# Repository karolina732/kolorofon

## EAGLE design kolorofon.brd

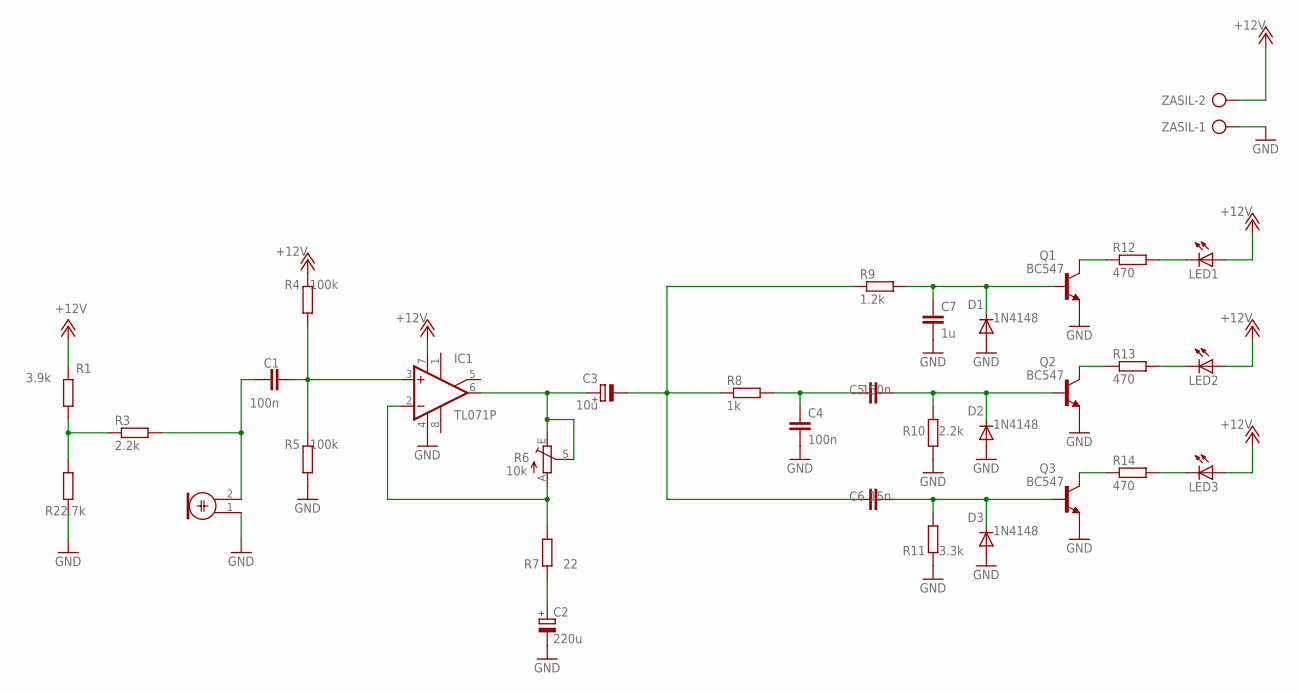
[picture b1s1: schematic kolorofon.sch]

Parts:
C1, C4: 100n; C050-025X075
C2: 220u; E2,5-6E
C3: 10u; E2-5
C5: 150n; C050-025X075
C6: 15n; C050-025X075
C7: 1u; C050-045X075
D1, D2, D3: 1N4148; DO35-7
IC1: TL071P; DIL08
LED1, LED2, LED3: LED5MM
M1: WM.64PN; WM-64PN
Q1, Q2, Q3: BC547; TO92
R1: 3.9k; 0204/7
R2: 2.7k; 0204/7
R3, R10: 2.2k; 0204/7
R4, R5: 100k; 0204/7
R6: 10k; S64Y
R7: 22; 0204/7
R8: 1k; 0204/7
R9: 1.2k; 0204/7
R11: 3.3k; 0204/7
R12, R13, R14: 470; 0204/7
ZASIL: AK300/2

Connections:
+12V: IC1.7 (V+), LED1.A, LED2.A, LED3.A, R1.1, R4.2, ZASIL.2
GND: C2.-, C4.2, C7.2, D1.A, D2.A, D3.A, IC1.4 (V-), M1.1, Q1.1 (E), Q2.1 (E), Q3.1 (E), R2.1, R5.1, R10.1, R11.1, ZASIL.1
unnamed: LED1.K (C), R12.2
unnamed: LED2.K (C), R13.2
unnamed: LED3.K (C), R14.2
unnamed: Q1.3 (C), R12.1
unnamed: Q2.3 (C), R13.1
unnamed: Q3.3 (C), R14.1
unnamed: C7.1, D1.C, Q1.2 (B), R9.2
unnamed: C5.2, D2.C, Q2.2 (B), R10.2
unnamed: C4.1, C5.1, R8.2
unnamed: C6.2, D3.C, Q3.2 (B), R11.2
unnamed: C3.-, C6.1, R8.1, R9.1
unnamed: C3.+, IC1.6 (OUT), R6.E, R6.S
unnamed: IC1.2 (-IN), R6.A, R7.2
unnamed: C2.+, R7.1
unnamed: C1.2, IC1.3 (+IN), R4.1, R5.2
unnamed: C1.1, M1.2, R3.2
unnamed: R1.2, R2.2, R3.1

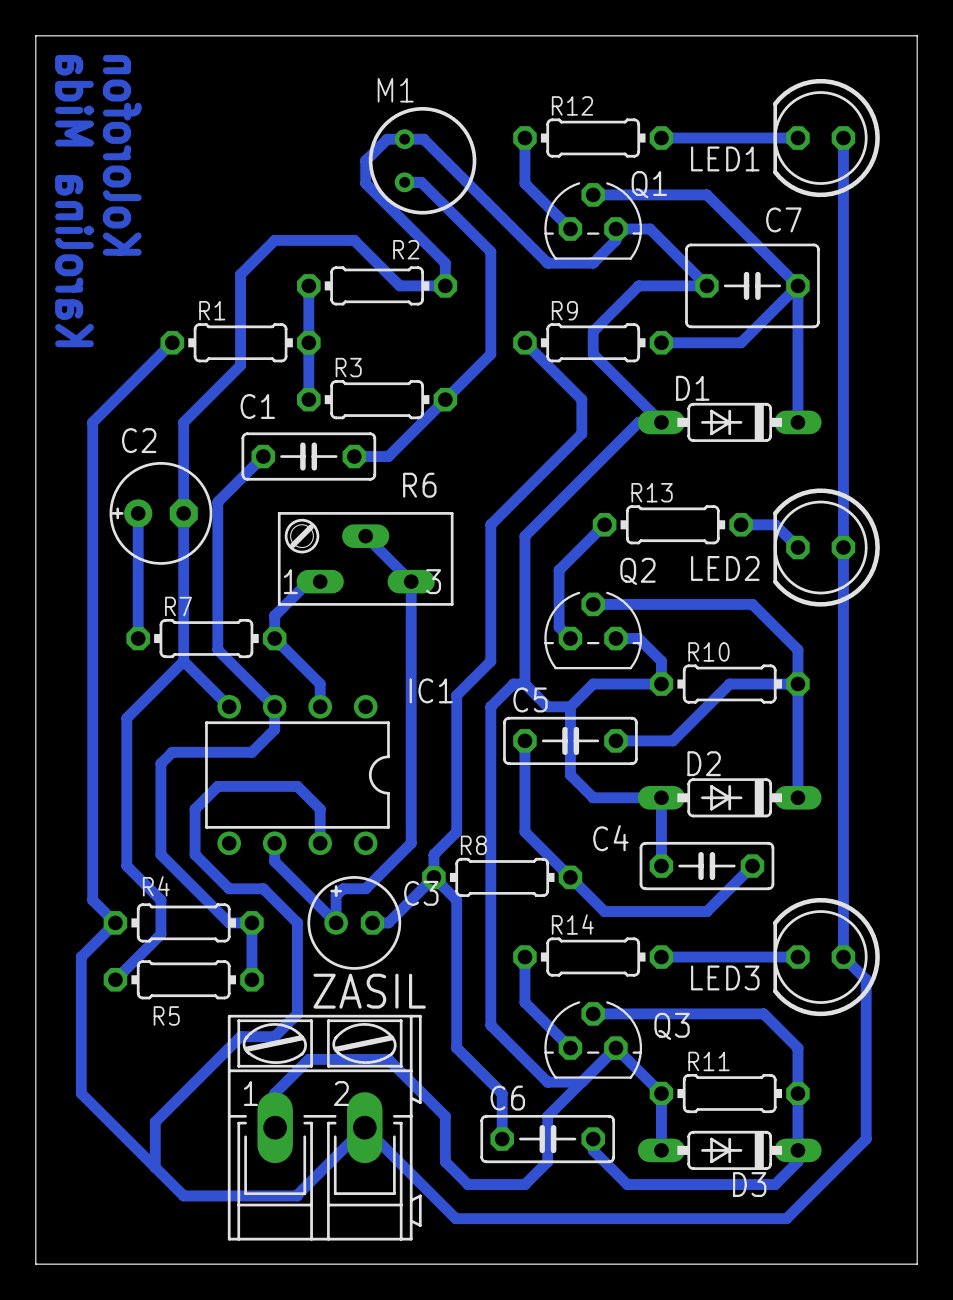
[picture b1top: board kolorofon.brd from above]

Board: 2 copper layers, 49.2 x 68.6 mm, 33 parts (0 on the bottom side), 19 nets.
